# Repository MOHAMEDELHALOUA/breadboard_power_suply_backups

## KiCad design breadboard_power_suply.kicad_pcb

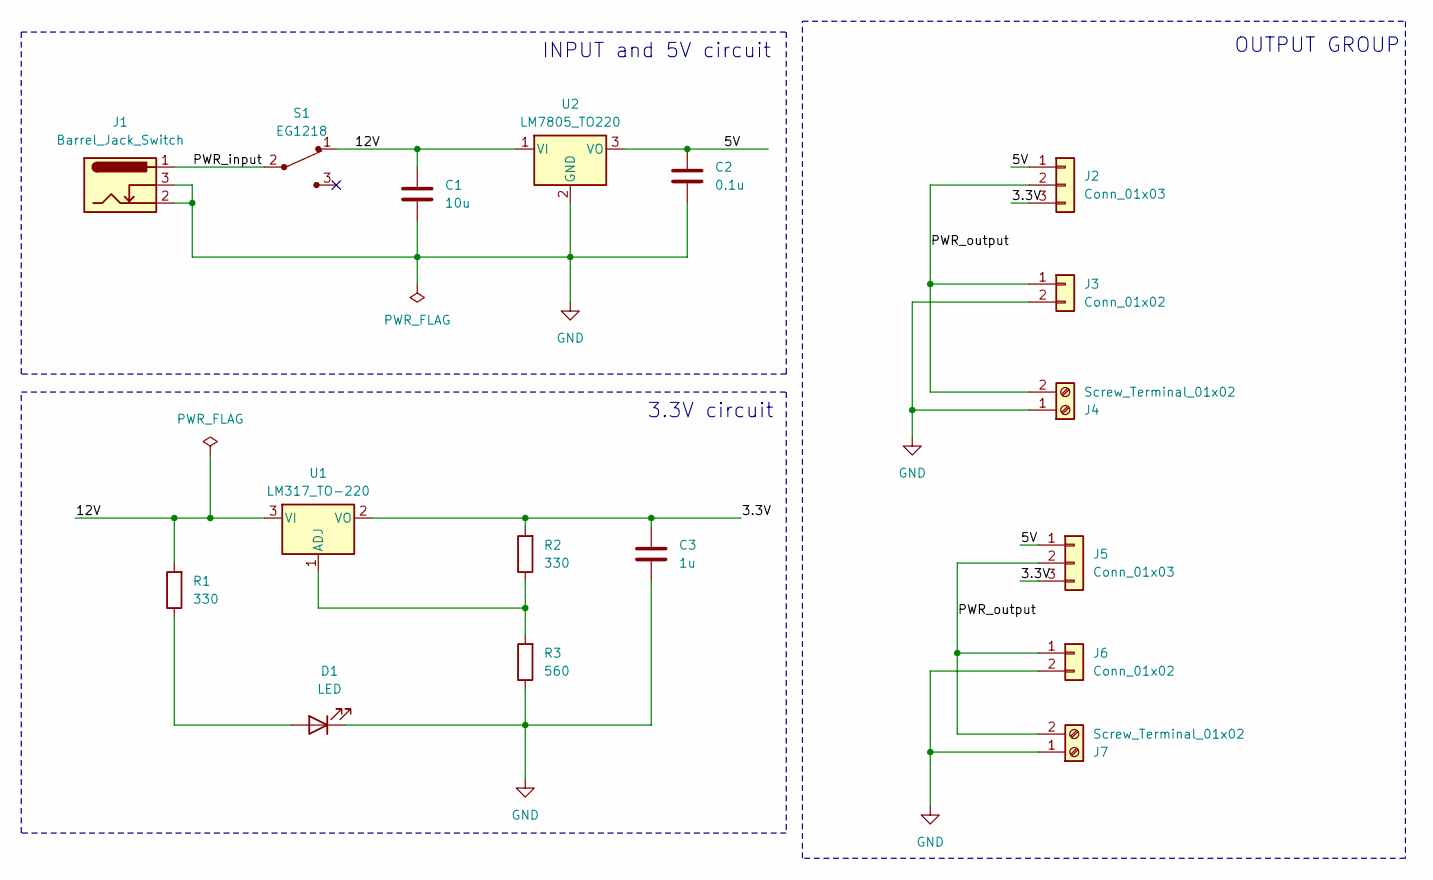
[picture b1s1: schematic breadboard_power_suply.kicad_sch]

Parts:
C1: 10u; C_Disc_D3.0mm_W1.6mm_P2.50mm
C2: 0.1u; C_Disc_D3.0mm_W1.6mm_P2.50mm
C3: 1u; C_Disc_D3.0mm_W1.6mm_P2.50mm
D1: LED; LED_D5.0mm
J1: Barrel_Jack_Switch; BarrelJack_Horizontal
J2, J5: Conn_01x03; PinHeader_1x03_P2.54mm_Vertical
J3, J6: Conn_01x02; PinHeader_1x02_P2.54mm_Vertical
J4, J7: Screw_Terminal_01x02; TerminalBlock_bornier-2_P5.08mm
R1, R2: 330; R_Axial_DIN0204_L3.6mm_D1.6mm_P7.62mm_Horizontal
R3: 560; R_Axial_DIN0204_L3.6mm_D1.6mm_P7.62mm_Horizontal
S1: EG1218; Switch_Slide_11.6x4mm_EG1218; MPN EG1218; Digi-Key_PN EG1903-ND
U1: LM317_TO-220; TO-220-3_Vertical
U2: LM7805_TO220; TO-220-3_Vertical

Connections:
/3.3V: C3.1, J2.3, J5.3, R2.2, U1.2 (VO)
/5V: C2.1, J2.1, J5.1, U2.3 (VO)
/12V: C1.1, R1.2, S1.1, U1.3 (VI), U2.1 (VI)
/PWR_input: J1.1, S1.2
/PWR_output: J2.2, J3.1, J4.2, J5.2, J6.1, J7.2
GND: C1.2, C2.2, C3.2, D1.1 (K), J1.2, J1.3, J3.2, J4.1, J6.2, J7.1, R3.1, U2.2 (GND)
unnamed: D1.2 (A), R1.1
unnamed: R2.1, R3.2, U1.1 (ADJ)

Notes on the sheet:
3.3V circuit
OUTPUT GROUP
INPUT and 5V circuit

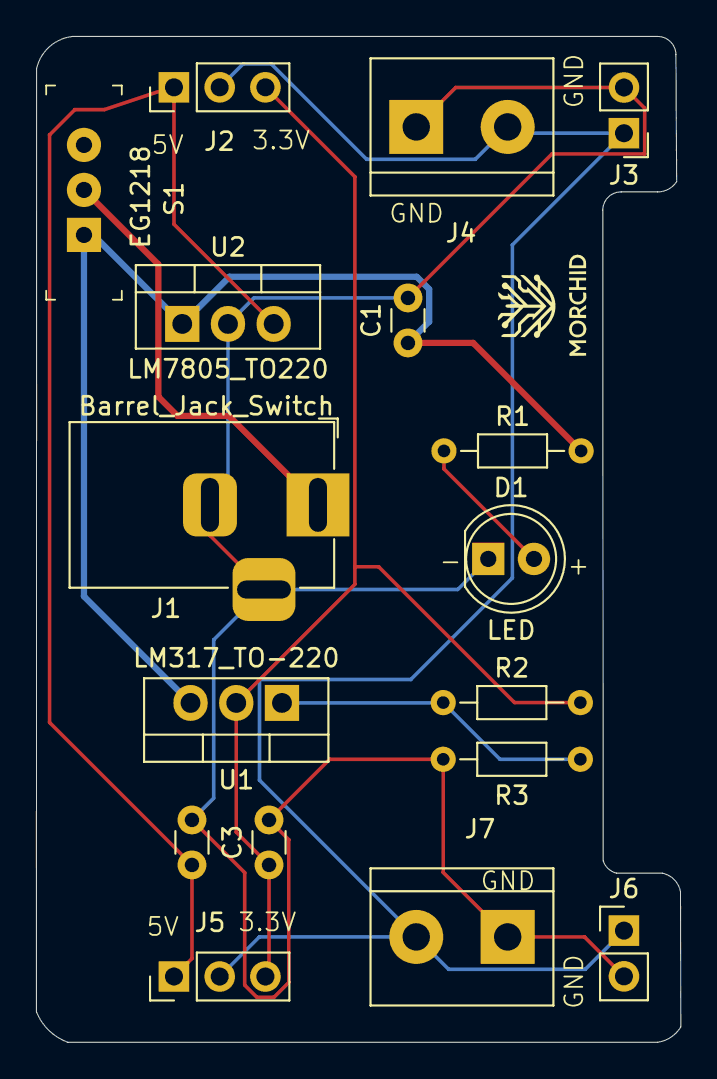
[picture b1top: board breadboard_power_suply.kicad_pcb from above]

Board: 2 copper layers, 35.8 x 55.9 mm, 17 parts (0 on the bottom side), 8 nets.

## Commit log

2024-08-05 Rename output-1.png to Schematic.png
